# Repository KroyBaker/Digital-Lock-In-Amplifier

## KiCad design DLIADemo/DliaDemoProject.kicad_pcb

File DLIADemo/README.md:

The first test for designing the DLIA on KiCad

Some problems I faced were
      -Component management
      -Trace Implementation
      -No hierarchal sheets
      -Difficult readability

I intend on fixing this for my next design, nearly all the componenets will be the same as they have been properly finalized.

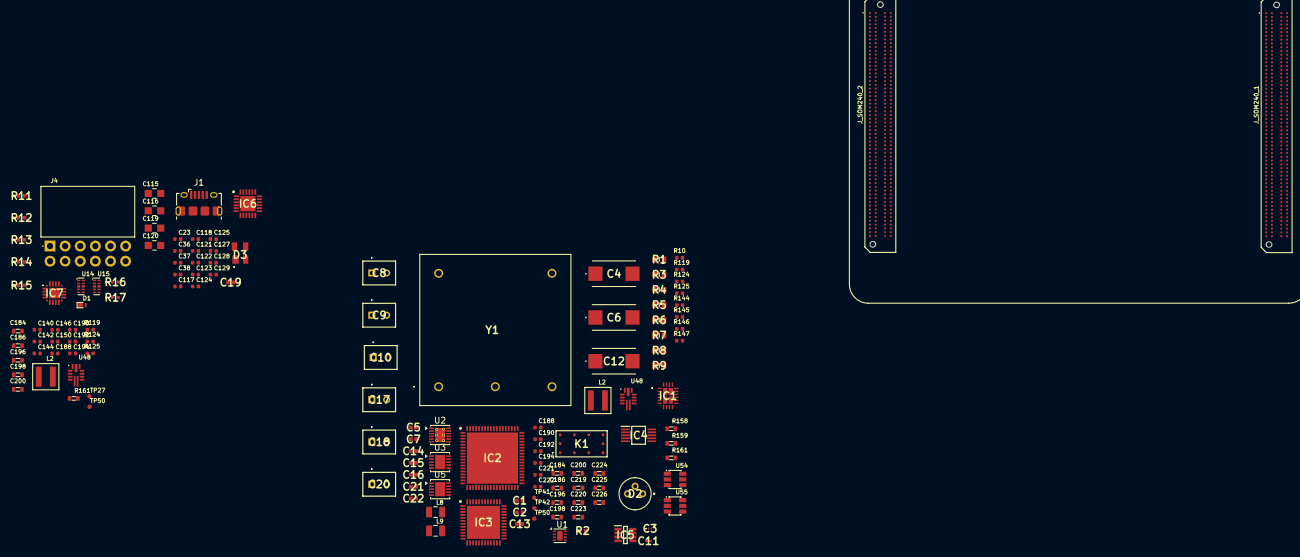
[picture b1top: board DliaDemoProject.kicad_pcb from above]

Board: 6 copper layers, 137 parts (0 on the bottom side), 106 nets, no tracks yet.

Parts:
C1, C2: 47pF; CAPC1005X70N
C3: 0.1pF; GRM033D70J224ME01D
C4, C6, C12: 10uF; T510X
C5, C7, C14, C15, C16, C21, C22: 0.1uF; CAPC1005X56N
C8, C9, C10, C17, C18, C20: 4.7 uF; RCER71H475K3DBH03A
C11: 10pF; CAPC0603X33N
C13: 0.1uF; CAPC1005X70N
C19: GRM155R71C104KA88D; CAPC1005X70N
C23, C190, C190#2: C_3n9_0402; C_0402_1005Metric
C36, C117, C121, C188, C188#2: C_1u_0402; C_0402_1005Metric
C37, C38, C118, C122, C124, C125, C128, C129, C140, C142, C144, C146, C192, C192#2, C221, C222: C_100n_0402; C_0402_1005Metric
C115, C116, C119, C120: C_47u_0805; C_0805_2012Metric
C123, C127, C150: C_4u7_0402; C_0402_1005Metric
C184, C184#2, C186, C186#2, C219, C220: C_10u_25V_0603; C_0603_1608Metric
C194, C194#2: C_22p_0402; C_0402_1005Metric
C196, C196#2, C198, C198#2, C200, C200#2: C_22u_16V_0603; C_0603_1608Metric
C223, C224, C225, C226: C_22u_0603; C_0603_1608Metric
D1: PTVS5V0Z1USKP; SOD-964
D2: S5973
D3: SP0503BAHTG
IC1: LTC6419IV#PBF; LTC6419IVPBF
IC2: AD9467SCPZ-250-EP; QFN50P1000X1000X90-73N-D
IC3: AD9517-4ABCPZ-RL7; QFN50P700X700X100-49N-D
IC4: AD9833WBRMZ-REEL; SOP50P490X110-10N
IC5: AD5680BRJZ-1500RL7; SOT65P280X145-8N
IC6: TXS02612RTWR; QFN50P400X400X80-25N-D
IC7: CP2102N-A02-GQFN20; CP2102NA02GQFN20
J1: USB_B_Micro; USB_Micro-B_Amphenol_10118194-0001LF_Horizontal
J4: PinSocket_2x6_P2.54mm_Drill1.04mm_Horizontal
J_SOM240_1, J_SOM240_2: ADM6-60-01.5-L-4-2-A-TR; Conn_Plug_Samtec_ADM6_4x60_ADM6-60-01.5-L-4-2-A-TR
K1: CRR03-1AS; CRR031AS
L2, L2#2: L_3u3_5.9A_XEL4030; L_Coilcraft-XEL4030
L8, L9: L_1u_2.6A_0806; L_0806_2016Metric
R1: TNPW060322R0BEEA; RESC1608X55N
R2: 10 kOhms; RESC1005X40N
R3, R6: 22ohm; RESC1608X55N
R4, R5, R8: 24.9 kOhm; RESC1608X55N
R7: 4.12 Kohm; RESC1608X55N
R9: 5.1 kΩ; RESC1608X55N
R10: R_0R_0402; R_0402_1005Metric
R11, R12, R13, R14, R15: CRCW040247K0JNED; CRCW0402200KFKED
R16: 47.5Kohm; ERA2AED122X
R17: 22.1Kohms; ERA2AED122X
R119, R119#2: R_100k_0402; R_0402_1005Metric
R124, R124#2: R_147k_0402; R_0402_1005Metric
R125, R125#2: R_24k_0402; R_0402_1005Metric
R144: R_31k6_0402; R_0402_1005Metric
R145, R147: R_10k_0402; R_0402_1005Metric
R146: R_4k99_0402; R_0402_1005Metric
R158, R159, R161, R161#2: R_0R_22.4A_0603; R_0603_1608Metric
TP27, TP41, TP42, TP50, TP50#2: TP_0.75mm_SMD; TP_SMD_0.75mm
U1: OPA855xDSG; WSON-8-1EP_2x2mm_P0.5mm_EP0.9x1.6mm
U2: LT3094xDD; DFN-12-1EP_3x3mm_P0.45mm_EP1.65x2.38mm_ThermalVias
U3, U5: LT3045xDD; DFN-10-1EP_3x3mm_P0.5mm_EP1.65x2.38mm
U14, U15: TPD4E05U06QDQARQ1; USON-10_2.5x1mm_P0.5mm
U48, U48#2: RT6236AHGQUF; UQFN-13_2x3mm_P0.5mm
U54, U55: AP62301_TSOT; TSOT23-6
Y1: OH100-50503CV-010.0M; OH10050503CV0100M

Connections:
+1V8: IC2.1 (AVDD1_1), IC2.2 (AVDD1_2), IC2.3 (AVDD1_3), IC2.4 (AVDD1_4), IC2.7 (AVDD1_5), IC2.8 (AVDD1_6), IC2.9 (AVDD1_7), IC2.11 (AVDD1_8), IC2.12 (AVDD1_9), IC2.13 (AVDD1_10), IC2.15 (AVDD1_11), IC2.37 (DRVDD_2), IC2.42 (AVDD3_1), IC2.44 (AVDD3_2), IC2.46 (AVDD1_12), IC2.52 (AVDD1_13), IC2.53 (AVDD1_14), IC2.54 (AVDD1_15), IC2.55 (AVDD1_16), IC2.56 (AVDD1_17), IC2.58 (AVDD1_18), IC2.59 (AVDD1_19), IC2.60 (AVDD1_20), IC2.61 (AVDD1_21), IC2.62 (AVDD1_22), IC2.63 (AVDD1_23), IC2.70 (AVDD1_24), IC2.71 (AVDD1_25), IC2.72 (AVDD1_26), IC6.5 (VCCA)
+3.3V: IC2.64 (AVDD2_1), IC2.65 (AVDD2_2), IC2.68 (AVDD2_3), IC2.69 (AVDD2_4), IC6.17 (VCCB1), IC6.21 (VCCB0), R11.1, R12.1, R13.1, R14.1, R15.1
+5V: C18.1, C20.1, C21.1, IC3.3 (VCP), U3.1 (IN), U3.2 (IN), Y1.5 (SUPPLY_VOLTAGE_(VCC))
-5V: C17.1, U2.1 (IN), U2.2 (IN), U2.13 (IN)
/AVDD_5: C12.1 (+), C14.2, IC1.12 (V+B), IC1.15 (V+A), U5.9 (OUTS), U5.10 (OUT)
/DC_MAIN_BUS: C184#2.1, C186.1, C219.1, C220.1, R119#2.2, U48#2.9 (VIN), U48#2.10 (VIN), U54.3 (VIN), U55.3 (VIN)
/HDA11: J4.1, J_SOM240_1.A17, U14.1, U14.10
/HDA12: J4.3, J_SOM240_1.D20, U14.2, U14.9
/HDA13: J4.5, J_SOM240_1.D21, U14.4, U14.7
/HDA14: J4.7, J_SOM240_1.D22, U14.5, U14.6
/HDA15: J4.2, J_SOM240_1.B20, U15.1, U15.10
/HDA16_CC: J4.4, J_SOM240_1.B21, U15.2, U15.9
/HDA17: J4.6, J_SOM240_1.B22, U15.4, U15.7
/HDA18: J4.8, J_SOM240_1.C22, U15.5, U15.6
/HPA00_CC_N: IC2.27 (DCO-), J_SOM240_1.C04
/HPA00_CC_P: IC2.28 (DCO+), J_SOM240_1.C03
/HPA01_N: IC2.19 (D1-/D0-), J_SOM240_1.D08
/HPA01_P: IC2.20 (D1+/D0+), J_SOM240_1.D07
/HPA02_N: IC2.21 (D3-/D2-), IC2.22 (D3+/D2+), J_SOM240_1.D05
/HPA03_N: IC2.23 (D5-/D4-), J_SOM240_1.C07
/HPA03_P: IC2.24 (D5+/D4+), J_SOM240_1.C06
/HPA04_N: IC2.25 (D7-/D6-), J_SOM240_1.B05
/HPA04_P: IC2.26 (D7+/D6+), J_SOM240_1.B04
/HPA06_N: IC2.31 (D11-/D10-), J_SOM240_1.A04
/HPA06_P: IC2.32 (D11+/D10+), J_SOM240_1.A03
/HPA07_N: IC2.33 (D13-/D12-), J_SOM240_1.B08
/HPA07_P: IC2.34 (D13+/D12+), J_SOM240_1.B07
/HPA08_N: IC2.35 (D15-/D14-), J_SOM240_1.C10
/HPA08_P: IC2.36 (D15+/D14+), J_SOM240_1.C09
/HPA09_N: IC2.39 (OR-), J_SOM240_1.D11
/HPA09_P: IC2.40 (OR+), J_SOM240_1.D10
/MIO36: IC7.18 (TXD), J_SOM240_1.B29
/MIO37: IC7.17 (RXD), J_SOM240_1.B30
/MIO38: IC2.48 (SDIO), J_SOM240_1.B32
/MIO39: IC2.49 (SCLK), J_SOM240_1.B33
/MIO40: IC2.50 (CSB), J_SOM240_1.B34
/MIO44: IC6.9 (CLKA), J_SOM240_1.D32
/MIO45: IC6.4 (CMDA), J_SOM240_1.D33
/MIO46: IC6.6 (DAT0A), J_SOM240_1.D34
/MIO47: IC6.7 (DAT1A), J_SOM240_1.C34
/MIO48: IC6.1 (DAT2A), J_SOM240_1.C35
/MIO49: IC6.3 (DAT3A), J_SOM240_1.C36
/PL_1V2_OUT: C224.1, C226.1, L9.2, R146.1, R159.1, TP42.1
/PL_3V3_OUT: C223.2, C225.2, L8.2, R144.1, R158.1, TP41.1
/SOM Decoupling/DC_MAIN_BUS: C184.1, C186#2.1, R119.2, U48.9 (VIN), U48.10 (VIN)
/SOM Decoupling/SOM_5V_FB: C194#2.2, R124.1
/SOM Decoupling/SOM_5V_OUT: C196.1, C198.1, C200.1, L2#2.2, R161#2.1, TP50#2.1
/SOM Decoupling/SW_SOM_5V: C192#2.2, L2#2.1, U48.12 (SW)
/SOM Decoupling/USB_3V3: C140.1, C142.1, C144.1, C146.1, C150.2, TP27.1
/SOM_5V_FB: C194.2, R124#2.1
/SOM_5V_OUT: C196#2.1, C198#2.1, C200#2.1, L2.2, R161.1, TP50.1
/SW_PL_1V2: C222.2, L9.1, U55.2 (SW)
/SW_PL_3V3: C221.2, L8.1, U54.2 (SW)
/SW_SOM_5V: C192.2, L2.1, U48#2.12 (SW)
/VCCOEN_PL_M2C: U54.5 (EN), U55.5 (EN)
/VCC_BATT: J_SOM240_1.A01, R10.2
AGND: C1.1, C2.1, C4.1 (+), C5.1, C6.2 (-), C7.1, C8.2, C9.2, C10.2, C12.2 (-), C13.2, C14.1, C17.2, C18.2, C19.2, C20.2, C21.2, IC1.1 (-INA), IC1.13 (V-_1), IC1.14 (V-_2), IC1.21 (V-_3), IC1.22 (V-_4), IC1.23 (V-_5), IC1.24 (V-_6), IC2.10 (AGND_1), IC2.14 (AGND_2), IC2.16 (AGND_3), IC2.41 (AGND_4), IC2.43 (AGND_5), IC2.45 (AGND_6), IC2.73 (EPAD), IC3.49 (GND), R4.2, R5.2, R7.2, R8.1, R9.2, U1.4 (+), U2.9 (GND), U3.8 (GND), U3.11 (GND), U5.8 (GND), U5.11 (GND), Y1.2 (GROUND_(CASE))
DRGND: C23.2, D3.1 (COMMON_A), IC2.17 (DRGND_1), IC2.38 (DRGND_2), IC6.2 (GND_1), IC6.11 (GND_2), IC6.24 (SEL), IC6.25 (THERMAL_PAD), IC7.3 (GND_1), IC7.12 (GND_2), J1.5 (GND), R16.2
GND: C36.2, C37.2, C38.2, C115.2, C116.2, C117.2, C118.2, C119.2, C120.2, C121.2, C122.2, C123.2, C124.2, C125.2, C127.2, C128.2, C129.2, C140.2, C142.2, C144.2, C146.2, C150.1, C184.2, C184#2.2, C186.2, C186#2.2, C188.2, C188#2.2, C190.2, C190#2.2, C196.2, C196#2.2, C198.2, C198#2.2, C200.2, C200#2.2, C219.2, C220.2, C223.1, C224.2, C225.1, C226.2, D1.A, J4.9, J4.10, J_SOM240_1.A02, J_SOM240_1.A05, J_SOM240_1.A08, J_SOM240_1.A11, J_SOM240_1.A14, J_SOM240_1.A18, J_SOM240_1.A21, J_SOM240_1.A26, J_SOM240_1.A33, J_SOM240_1.A37, J_SOM240_1.A41, J_SOM240_1.A45, J_SOM240_1.A46, J_SOM240_1.A49, J_SOM240_1.A50, J_SOM240_1.A53, J_SOM240_1.A54, J_SOM240_1.A57, J_SOM240_1.A58, J_SOM240_1.B03, J_SOM240_1.B06, J_SOM240_1.B09, J_SOM240_1.B12, J_SOM240_1.B15, J_SOM240_1.B19, J_SOM240_1.B23, J_SOM240_1.B27, J_SOM240_1.B31, J_SOM240_1.B35, J_SOM240_1.B39, J_SOM240_1.B43, J_SOM240_1.B47, J_SOM240_1.B48, J_SOM240_1.B51, J_SOM240_1.B52, J_SOM240_1.B55, J_SOM240_1.B56, J_SOM240_1.B59, J_SOM240_1.C01, J_SOM240_1.C02, J_SOM240_1.C05, J_SOM240_1.C08, J_SOM240_1.C11, J_SOM240_1.C14, J_SOM240_1.C17, J_SOM240_1.C21, J_SOM240_1.C25, J_SOM240_1.C29, J_SOM240_1.C33, J_SOM240_1.C37, J_SOM240_1.C41, J_SOM240_1.C46, J_SOM240_1.C49, J_SOM240_1.C50, J_SOM240_1.C53, J_SOM240_1.C54, J_SOM240_1.C57, J_SOM240_1.C58, J_SOM240_1.D03, J_SOM240_1.D06, J_SOM240_1.D09, J_SOM240_1.D12, J_SOM240_1.D15, J_SOM240_1.D19, J_SOM240_1.D23, J_SOM240_1.D27, J_SOM240_1.D31, J_SOM240_1.D35, J_SOM240_1.D39, J_SOM240_1.D43, J_SOM240_1.D47, J_SOM240_1.D48, J_SOM240_1.D51, J_SOM240_1.D52, J_SOM240_1.D55, J_SOM240_1.D56, J_SOM240_1.D59, J_SOM240_2.A01, J_SOM240_2.A02, J_SOM240_2.A05, J_SOM240_2.A06, J_SOM240_2.A09, J_SOM240_2.A10, J_SOM240_2.A13, J_SOM240_2.A16, J_SOM240_2.A19, J_SOM240_2.A22, J_SOM240_2.A25, J_SOM240_2.A28, J_SOM240_2.A31, J_SOM240_2.A34, J_SOM240_2.A37, J_SOM240_2.A40, J_SOM240_2.A43, J_SOM240_2.A45, J_SOM240_2.A49, J_SOM240_2.A53, J_SOM240_2.A57, J_SOM240_2.B03, J_SOM240_2.B04, J_SOM240_2.B07, J_SOM240_2.B08, J_SOM240_2.B11, J_SOM240_2.B14, J_SOM240_2.B17, J_SOM240_2.B20, J_SOM240_2.B23, J_SOM240_2.B26, J_SOM240_2.B29, J_SOM240_2.B32, J_SOM240_2.B35, J_SOM240_2.B38, J_SOM240_2.B41, J_SOM240_2.B43, J_SOM240_2.B47, J_SOM240_2.B51, J_SOM240_2.B55, J_SOM240_2.C01, J_SOM240_2.C02, J_SOM240_2.C05, J_SOM240_2.C06, J_SOM240_2.C09, J_SOM240_2.C10, J_SOM240_2.C13, J_SOM240_2.C16, J_SOM240_2.C19, J_SOM240_2.C22, J_SOM240_2.C25, J_SOM240_2.C28, J_SOM240_2.C31, J_SOM240_2.C34, J_SOM240_2.C37, J_SOM240_2.C40, J_SOM240_2.C43, J_SOM240_2.C45, J_SOM240_2.C49, J_SOM240_2.C53, J_SOM240_2.C57, J_SOM240_2.D03, J_SOM240_2.D04, J_SOM240_2.D07, J_SOM240_2.D08, J_SOM240_2.D11, J_SOM240_2.D14, J_SOM240_2.D17, J_SOM240_2.D20, J_SOM240_2.D23, J_SOM240_2.D26, J_SOM240_2.D29, J_SOM240_2.D32, J_SOM240_2.D35, J_SOM240_2.D38, J_SOM240_2.D41, J_SOM240_2.D43, J_SOM240_2.D47, J_SOM240_2.D51, J_SOM240_2.D55, R10.1, R125.2, R125#2.2, R145.2, R147.2, U14.3, U14.8, U15.3, U15.8, U48.1 (GND), U48.13 (GND), U48#2.1 (GND), U48#2.13 (GND), U54.1 (GND), U55.1 (GND)
unnamed: C4.2 (-), C5.2, U1.5 (V-), U1.9 (V-), U2.10 (OUTS), U2.11 (OUT), U2.12 (OUT)
unnamed: C6.1 (+), C7.2, U1.7 (V+), U1.8 (~PD), U3.9 (OUTS), U3.10 (OUT)
unnamed: C15.1, R3.2
unnamed: C16.1, R6.2
unnamed: D2.2 (CASE), K1.10 (COM), U1.3 (-)
unnamed: D3.2 (K_1), IC7.5 (D-), J1.2 (D-)
unnamed: D3.3 (K_2), IC7.4 (D+), J1.3 (D+)
unnamed: D3.4 (K_3), J1.1 (VBUS), R17.1
unnamed: IC1.20 (+INA), R1.2
unnamed: IC1.11 (+OUTB), R3.1
unnamed: IC1.10 (-OUTB), R6.1
unnamed: C13.1, IC1.9 (VOCMB)
unnamed: IC2.5 (CLK+), IC3.39 (OUT1)
unnamed: IC2.6 (CLK-), IC3.38 (~OUT1)
unnamed: C2.2, C11.2, C15.2, IC2.66 (VIN+)
unnamed: C1.2, C11.1, C16.2, IC2.67 (VIN-)
unnamed: C19.1, IC2.57 (XVREF)
unnamed: IC3.46 (CPRSET), R9.1
unnamed: C22.1, IC3.48 (REFIN_(REF1))
unnamed: IC3.44 (RSET), R7.1
unnamed: IC6.20 (CMDB0), R13.2
unnamed: IC6.14 (DAT0B1), R15.2
unnamed: IC6.16 (DAT1B0), R14.2
unnamed: IC6.23 (DAT2B0), R11.2
unnamed: IC6.22 (DAT3B0), R12.2
unnamed: IC7.8 (VBUS), R16.1, R17.2
unnamed: C23.1, J1.6 (Shield)
unnamed: C3.1, K1.5 (NO), R2.1
unnamed: R1.1, U1.6
unnamed: C3.2, R2.2, U1.1 (FB)
unnamed: C8.1, R5.1, U2.8 (SET)
unnamed: C9.1, R4.1, U3.7 (SET)
unnamed: U5.1 (IN), U5.2 (IN)
unnamed: C10.1, R8.2, U5.7 (SET)
unnamed: C192.1, C192#2.1, U48.11 (BOOT), U48#2.11 (BOOT)
unnamed: R119.1, R119#2.1, U48.2 (EN), U48#2.2 (EN)
unnamed: C194.1, C194#2.1, R124.2, R124#2.2, R125.1, R125#2.1, U48.3 (FB), U48#2.3 (FB)
unnamed: C188.1, C188#2.1, U48.6 (PVCC), U48#2.6 (PVCC)
unnamed: C190.1, C190#2.1, U48.5 (SS), U48#2.5 (SS)
unnamed: C221.1, U54.6 (BST)
unnamed: R144.2, R145.1, U54.4 (FB)
unnamed: C222.1, U55.6 (BST)
unnamed: R146.2, R147.1, U55.4 (FB)
unnamed: C22.2, Y1.1 (OUTPUT)
PL_3V3: C36.1, C37.1, C38.1, C127.1, C128.1, C129.1, D1.K, J4.11, J4.12, J_SOM240_1.B13, J_SOM240_1.B14, R158.2
SOM_5V0: C115.1, C116.1, C117.1, C118.1, C119.1, C120.1, C121.1, C122.1, J_SOM240_1.A59, J_SOM240_1.A60, J_SOM240_1.B60, J_SOM240_1.C59, J_SOM240_1.C60, J_SOM240_1.D60, R161.2, R161#2.2
VCCO_HPA: C123.1, C124.1, C125.1, IC2.51 (SPIVDD), J_SOM240_1.D01, J_SOM240_1.D02

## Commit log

2025-12-23 Implement sine, cosine, square wave, and DFT functions
    Added optimized sine and cosine functions, a square wave generator, and a Discrete Fourier Transform (DFT) implementation to analyze the frequency spectrum.
2025-12-29 Add comments for ARM functions and prototyping rationale
    Added comments explaining the use of ARM-specific functions for optimization and prototyping.
2025-12-29 Document project objective for Digital Lock In Amplifier
    Added project objective and design goals for the Digital Lock In Amplifier.
2025-12-30 Document ADC and AFE design considerations
    Added details about the ADC selection and AFE design, including the use of a Transimpedance Amplifier and a Butterworth low-pass filter.
2026-01-01 Refactor digital lock-in amplifier with Hanning window
    Refactored the digital lock-in amplifier code to improve frequency detection and added Hanning windowing to reduce spectral leakage. Adjusted sampling rate and buffer sizes for better performance.
2026-01-01 Enhance design rationale for ADC and AFE components
    Expanded the design rationale for the ADC and AFE, detailing component choices and their significance. Added information on the Low Pass Filter and Transimpedance Amplifier design considerations.
2026-01-04 Update design rationale to exclude MCU
    Removed MCU from project design in favor of FPGA.
2026-01-22 Add files via upload
    My first attempt designing the DLIA project, a couple issues I encountered were readability, scaling, and overall trace management.
2026-01-22 Create README.md for DLIA project
    Add initial README with project overview and challenges.

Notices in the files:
parts and their libraries:
License: Apache-2.0
